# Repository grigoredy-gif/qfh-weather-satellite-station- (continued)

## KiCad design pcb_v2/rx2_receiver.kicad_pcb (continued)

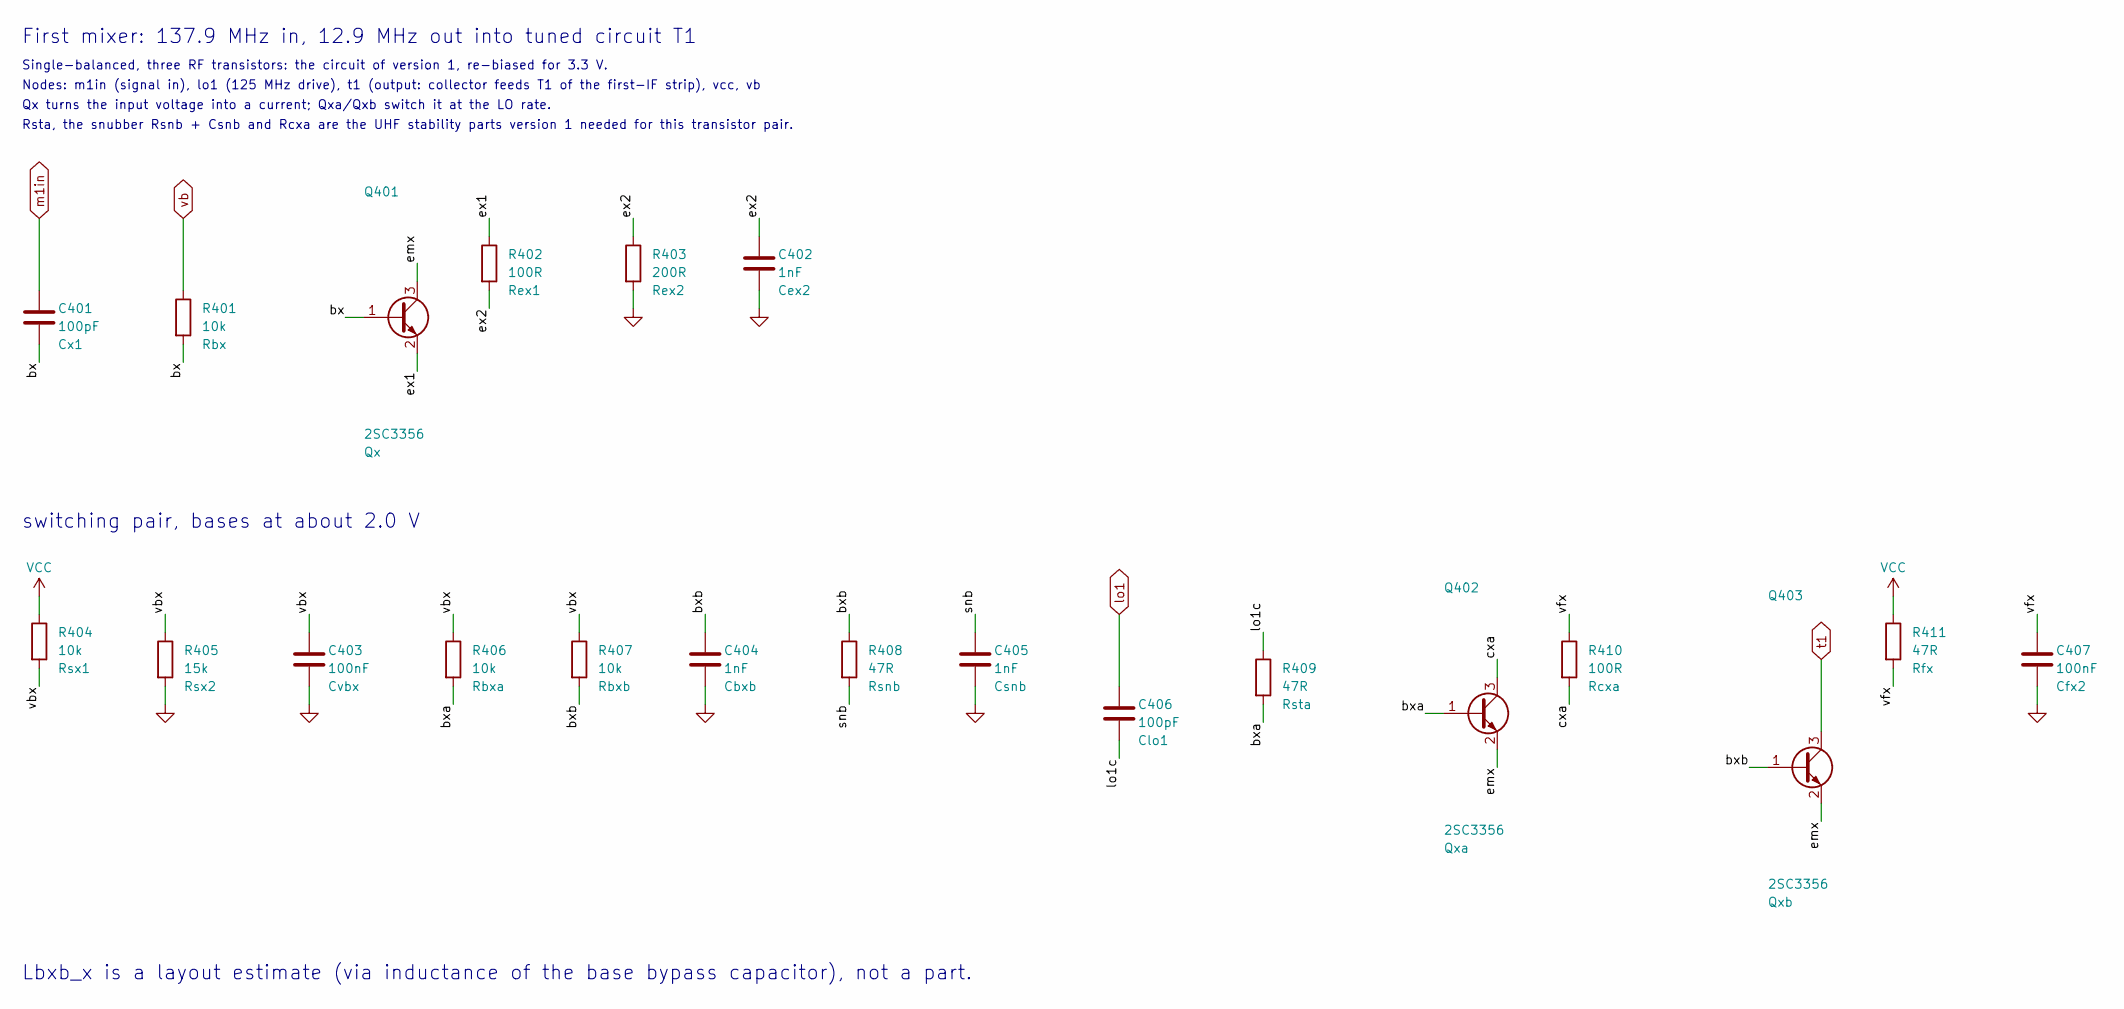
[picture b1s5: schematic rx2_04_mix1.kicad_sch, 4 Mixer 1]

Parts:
C401, C406: 100pF; C_0603_1608Metric; MPN CL10C101JB8NNNC; LCSC C14858
C402, C404, C405: 1nF; C_0603_1608Metric; MPN CL10B102KB8NNNC; LCSC C1588
C403, C407: 100nF; C_0603_1608Metric; MPN CC0603KRX7R9BB104; LCSC C14663
Q401, Q402, Q403: 2SC3356; SOT-23; MPN 2SC3356; LCSC C28646266
R401, R404, R406, R407: 10k; R_0603_1608Metric; MPN 0603WAF1002T5E; LCSC C25804
R402, R410: 100R; R_0603_1608Metric; MPN 0603WAF1000T5E; LCSC C22775
R403: 200R; R_0603_1608Metric; MPN 0603WAF2000T5E; LCSC C8218
R405: 15k; R_0603_1608Metric; MPN 0603WAF1502T5E; LCSC C22809
R408, R409, R411: 47R; R_0603_1608Metric; MPN 0603WAF470JT5E; LCSC C23182

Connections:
/4 Mixer 1/bx: C401.2, Q401.1 (B), R401.2
/4 Mixer 1/bxa: Q402.1 (B), R406.2, R409.2
/4 Mixer 1/bxb: C404.1, Q403.1 (B), R407.2, R408.1
/4 Mixer 1/cxa: Q402.3 (C), R410.2
/4 Mixer 1/emx: Q401.3 (C), Q402.2 (E), Q403.2 (E)
/4 Mixer 1/ex1: Q401.2 (E), R402.1
/4 Mixer 1/ex2: C402.1, R402.2, R403.1
/4 Mixer 1/lo1c: C406.2, R409.1
/4 Mixer 1/snb: C405.1, R408.2
/4 Mixer 1/vbx: C403.1, R404.2, R405.1, R406.1, R407.1
/4 Mixer 1/vfx: C407.1, R410.1, R411.2
GND: C402.2, C403.2, C404.2, C405.2, C407.2, R403.2, R405.2; also elsewhere on the board
VCC: R404.1, R411.1; also elsewhere on the board
lo1: C406.1; also elsewhere on the board
m1in: C401.1; also elsewhere on the board
t1: Q403.3 (C); also elsewhere on the board
vb: R401.1; also elsewhere on the board

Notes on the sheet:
First mixer: 137.9 MHz in, 12.9 MHz out into tuned circuit T1
Single-balanced, three RF transistors: the circuit of version 1, re-biased for 3.3 V.
Nodes: m1in (signal in), lo1 (125 MHz drive), t1 (output: collector feeds T1 of the first-IF strip), vcc, vb
Qx turns the input voltage into a current; Qxa/Qxb switch it at the LO rate.
Rsta, the snubber Rsnb + Csnb and Rcxa are the UHF stability parts version 1 needed for this transistor pair.
switching pair, bases at about 2.0 V
Lbxb_x is a layout estimate (via inductance of the base bypass capacitor), not a part.

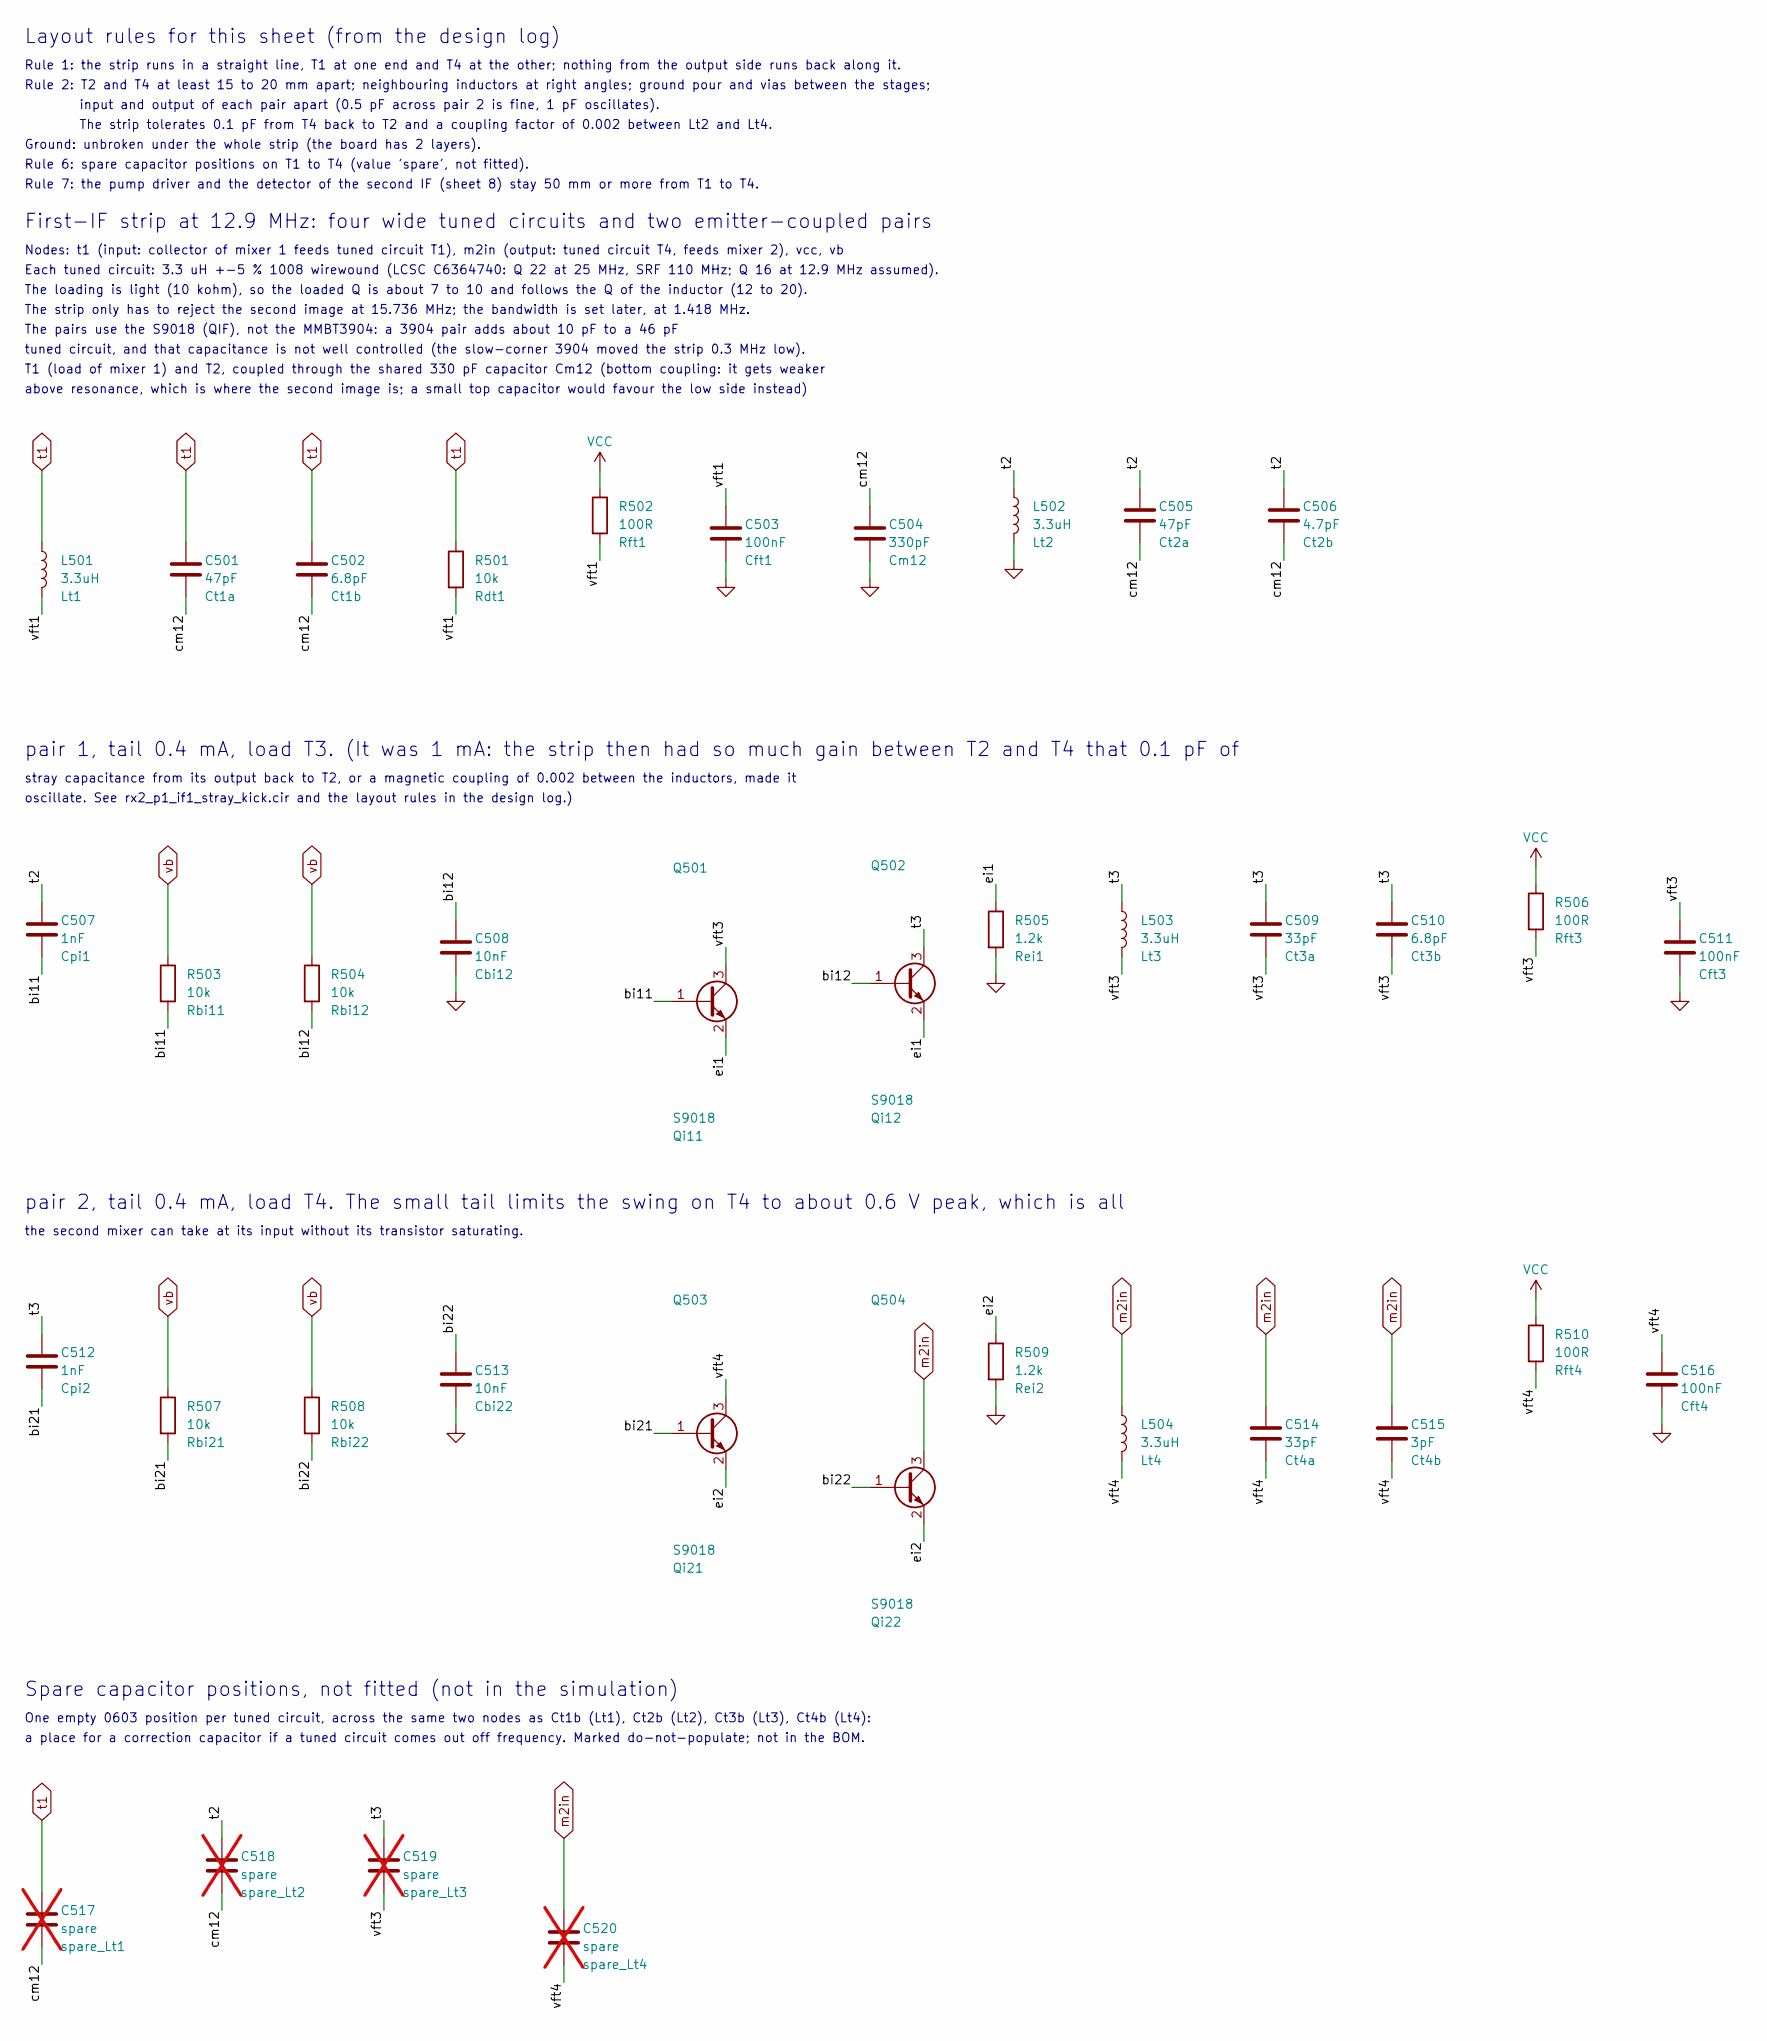
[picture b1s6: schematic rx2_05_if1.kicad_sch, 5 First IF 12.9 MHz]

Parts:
C501, C505: 47pF; C_0603_1608Metric; MPN CL10C470JB8NNNC; LCSC C1671
C502, C510: 6.8pF; C_0603_1608Metric; MPN 0603CG6R8C500NT; LCSC C1679
C503, C511, C516: 100nF; C_0603_1608Metric; MPN CC0603KRX7R9BB104; LCSC C14663
C504: 330pF; C_0603_1608Metric; MPN CL10C331JB8NNNC; LCSC C1664
C506: 4.7pF; C_0603_1608Metric; MPN 0603CG4R7C500NT; LCSC C1669
C507, C512: 1nF; C_0603_1608Metric; MPN CL10B102KB8NNNC; LCSC C1588
C508, C513: 10nF; C_0603_1608Metric; MPN 0603B103K500NT; LCSC C57112
C509, C514: 33pF; C_0603_1608Metric; MPN CL10C330JB8NNNC; LCSC C1663
C515: 3pF; C_0603_1608Metric; MPN 0603CG3R0C500NT; LCSC C46219
C517, C518, C519, C520: spare; C_0603_1608Metric; not fitted
L501, L502, L503, L504: 3.3uH; L_1008_AHW2520C; MPN AHW2520C-3R3JTF; LCSC C6364740
Q501, Q502, Q503, Q504: S9018; SOT-23; MPN S9018; LCSC C41375130
R501, R503, R504, R507, R508: 10k; R_0603_1608Metric; MPN 0603WAF1002T5E; LCSC C25804
R502, R506, R510: 100R; R_0603_1608Metric; MPN 0603WAF1000T5E; LCSC C22775
R505, R509: 1.2k; R_0603_1608Metric; MPN 0603WAF1201T5E; LCSC C22765

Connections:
/5 First IF 12.9 MHz/bi11: C507.2, Q501.1 (B), R503.2
/5 First IF 12.9 MHz/bi12: C508.1, Q502.1 (B), R504.2
/5 First IF 12.9 MHz/bi21: C512.2, Q503.1 (B), R507.2
/5 First IF 12.9 MHz/bi22: C513.1, Q504.1 (B), R508.2
/5 First IF 12.9 MHz/cm12: C501.2, C502.2, C504.1, C505.2, C506.2, C517.2, C518.2
/5 First IF 12.9 MHz/ei1: Q501.2 (E), Q502.2 (E), R505.1
/5 First IF 12.9 MHz/ei2: Q503.2 (E), Q504.2 (E), R509.1
/5 First IF 12.9 MHz/t2: C505.1, C506.1, C507.1, C518.1, L502.1
/5 First IF 12.9 MHz/t3: C509.1, C510.1, C512.1, C519.1, L503.1, Q502.3 (C)
/5 First IF 12.9 MHz/vft1: C503.1, L501.2, R501.2, R502.2
/5 First IF 12.9 MHz/vft3: C509.2, C510.2, C511.1, C519.2, L503.2, Q501.3 (C), R506.2
/5 First IF 12.9 MHz/vft4: C514.2, C515.2, C516.1, C520.2, L504.2, Q503.3 (C), R510.2
GND: C503.2, C504.2, C508.2, C511.2, C513.2, C516.2, L502.2, R505.2, R509.2; also elsewhere on the board
VCC: R502.1, R506.1, R510.1; also elsewhere on the board
m2in: C514.1, C515.1, C520.1, L504.1, Q504.3 (C); also elsewhere on the board
t1: C501.1, C502.1, C517.1, L501.1, R501.1; also elsewhere on the board
vb: R503.1, R504.1, R507.1, R508.1; also elsewhere on the board

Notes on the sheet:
Layout rules for this sheet (from the design log)
Rule 1: the strip runs in a straight line, T1 at one end and T4 at the other; nothing from the output side runs back along it.
Rule 2: T2 and T4 at least 15 to 20 mm apart; neighbouring inductors at right angles; ground pour and vias between the stages;
input and output of each pair apart (0.5 pF across pair 2 is fine, 1 pF oscillates).
The strip tolerates 0.1 pF from T4 back to T2 and a coupling factor of 0.002 between Lt2 and Lt4.
Ground: unbroken under the whole strip (the board has 2 layers).
Rule 6: spare capacitor positions on T1 to T4 (value 'spare', not fitted).
Rule 7: the pump driver and the detector of the second IF (sheet 8) stay 50 mm or more from T1 to T4.
First-IF strip at 12.9 MHz: four wide tuned circuits and two emitter-coupled pairs
Nodes: t1 (input: collector of mixer 1 feeds tuned circuit T1), m2in (output: tuned circuit T4, feeds mixer 2), vcc, vb
Each tuned circuit: 3.3 uH +-5 % 1008 wirewound (LCSC C6364740: Q 22 at 25 MHz, SRF 110 MHz; Q 16 at 12.9 MHz assumed).
The loading is light (10 kohm), so the loaded Q is about 7 to 10 and follows the Q of the inductor (12 to 20).
The strip only has to reject the second image at 15.736 MHz; the bandwidth is set later, at 1.418 MHz.
The pairs use the S9018 (QIF), not the MMBT3904: a 3904 pair adds about 10 pF to a 46 pF
tuned circuit, and that capacitance is not well controlled (the slow-corner 3904 moved the strip 0.3 MHz low).
T1 (load of mixer 1) and T2, coupled through the shared 330 pF capacitor Cm12 (bottom coupling: it gets weaker
above resonance, which is where the second image is; a small top capacitor would favour the low side instead)
pair 1, tail 0.4 mA, load T3. (It was 1 mA: the strip then had so much gain between T2 and T4 that 0.1 pF of
stray capacitance from its output back to T2, or a magnetic coupling of 0.002 between the inductors, made it
oscillate. See rx2_p1_if1_stray_kick.cir and the layout rules in the design log.)
pair 2, tail 0.4 mA, load T4. The small tail limits the swing on T4 to about 0.6 V peak, which is all
the second mixer can take at its input without its transistor saturating.
Spare capacitor positions, not fitted (not in the simulation)
One empty 0603 position per tuned circuit, across the same two nodes as Ct1b (Lt1), Ct2b (Lt2), Ct3b (Lt3), Ct4b (Lt4):
a place for a correction capacitor if a tuned circuit comes out off frequency. Marked do-not-populate; not in the BOM.

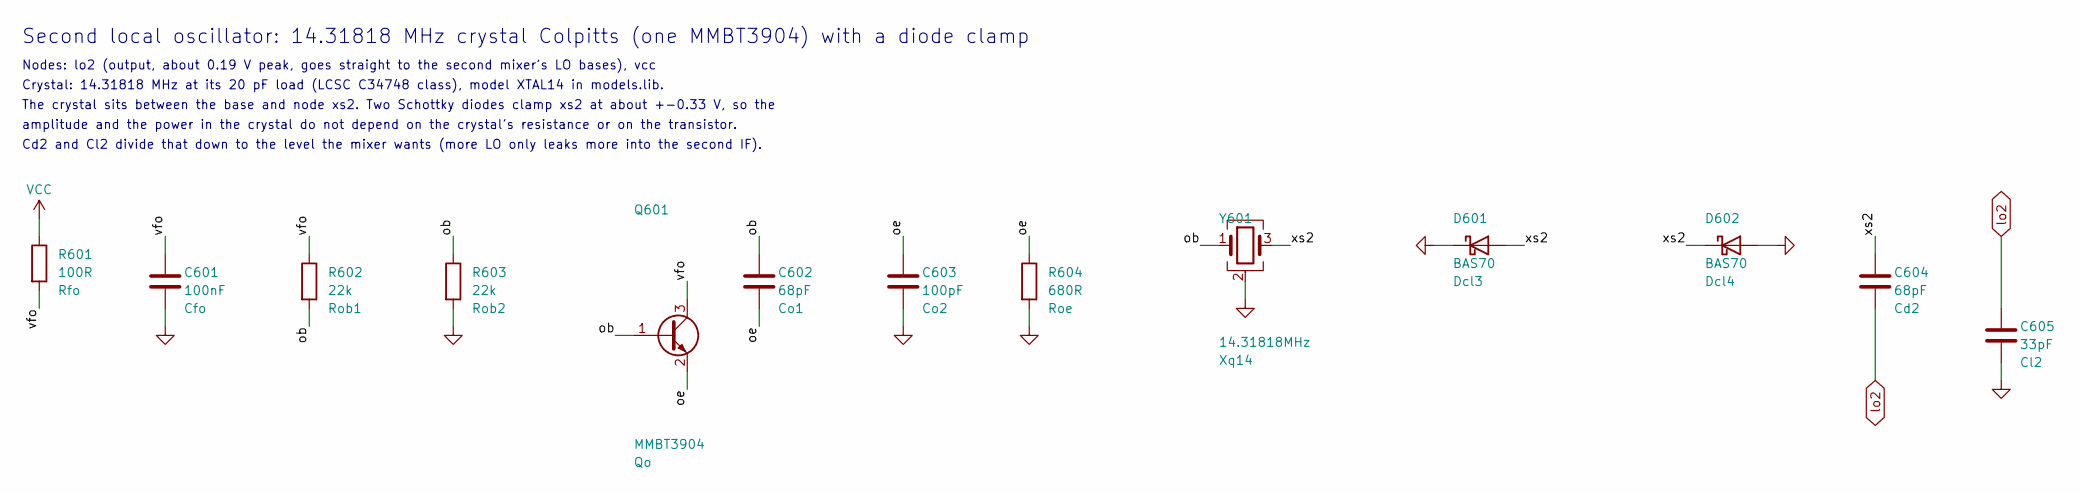
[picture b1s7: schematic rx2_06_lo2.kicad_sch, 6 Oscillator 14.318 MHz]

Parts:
C601: 100nF; C_0603_1608Metric; MPN CC0603KRX7R9BB104; LCSC C14663
C602, C604: 68pF; C_0603_1608Metric; MPN CL10C680JB8NNNC; LCSC C28262
C603: 100pF; C_0603_1608Metric; MPN CL10C101JB8NNNC; LCSC C14858
C605: 33pF; C_0603_1608Metric; MPN CL10C330JB8NNNC; LCSC C1663
D601, D602: BAS70; SOT-23; MPN BAS70; LCSC C7502686
Q601: MMBT3904; SOT-23; MPN MMBT3904(RANGE:100-300); LCSC C20526
R601: 100R; R_0603_1608Metric; MPN 0603WAF1000T5E; LCSC C22775
R602, R603: 22k; R_0603_1608Metric; MPN 0603WAF2202T5E; LCSC C31850
R604: 680R; R_0603_1608Metric; MPN 0603WAF6800T5E; LCSC C23228
Y601: 14.31818MHz; Crystal_SMD_3225-4Pin_3.2x2.5mm; MPN X32251431818MSB4SI; LCSC C34748

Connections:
/6 Oscillator 14.318 MHz/ob: C602.1, Q601.1 (B), R602.2, R603.1, Y601.1
/6 Oscillator 14.318 MHz/oe: C602.2, C603.1, Q601.2 (E), R604.1
/6 Oscillator 14.318 MHz/vfo: C601.1, Q601.3 (C), R601.2, R602.1
/6 Oscillator 14.318 MHz/xs2: C604.1, D601.1 (A), D602.3 (K), Y601.3
GND: C601.2, C603.2, C605.2, D601.3 (K), D602.1 (A), R603.2, R604.2, Y601.2 (G), Y601.4 (G); also elsewhere on the board
VCC: R601.1; also elsewhere on the board
lo2: C604.2, C605.1; also elsewhere on the board

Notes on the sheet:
Second local oscillator: 14.31818 MHz crystal Colpitts (one MMBT3904) with a diode clamp
Nodes: lo2 (output, about 0.19 V peak, goes straight to the second mixer's LO bases), vcc
Crystal: 14.31818 MHz at its 20 pF load (LCSC C34748 class), model XTAL14 in models.lib.
The crystal sits between the base and node xs2. Two Schottky diodes clamp xs2 at about +-0.33 V, so the
amplitude and the power in the crystal do not depend on the crystal's resistance or on the transistor.
Cd2 and Cl2 divide that down to the level the mixer wants (more LO only leaks more into the second IF).

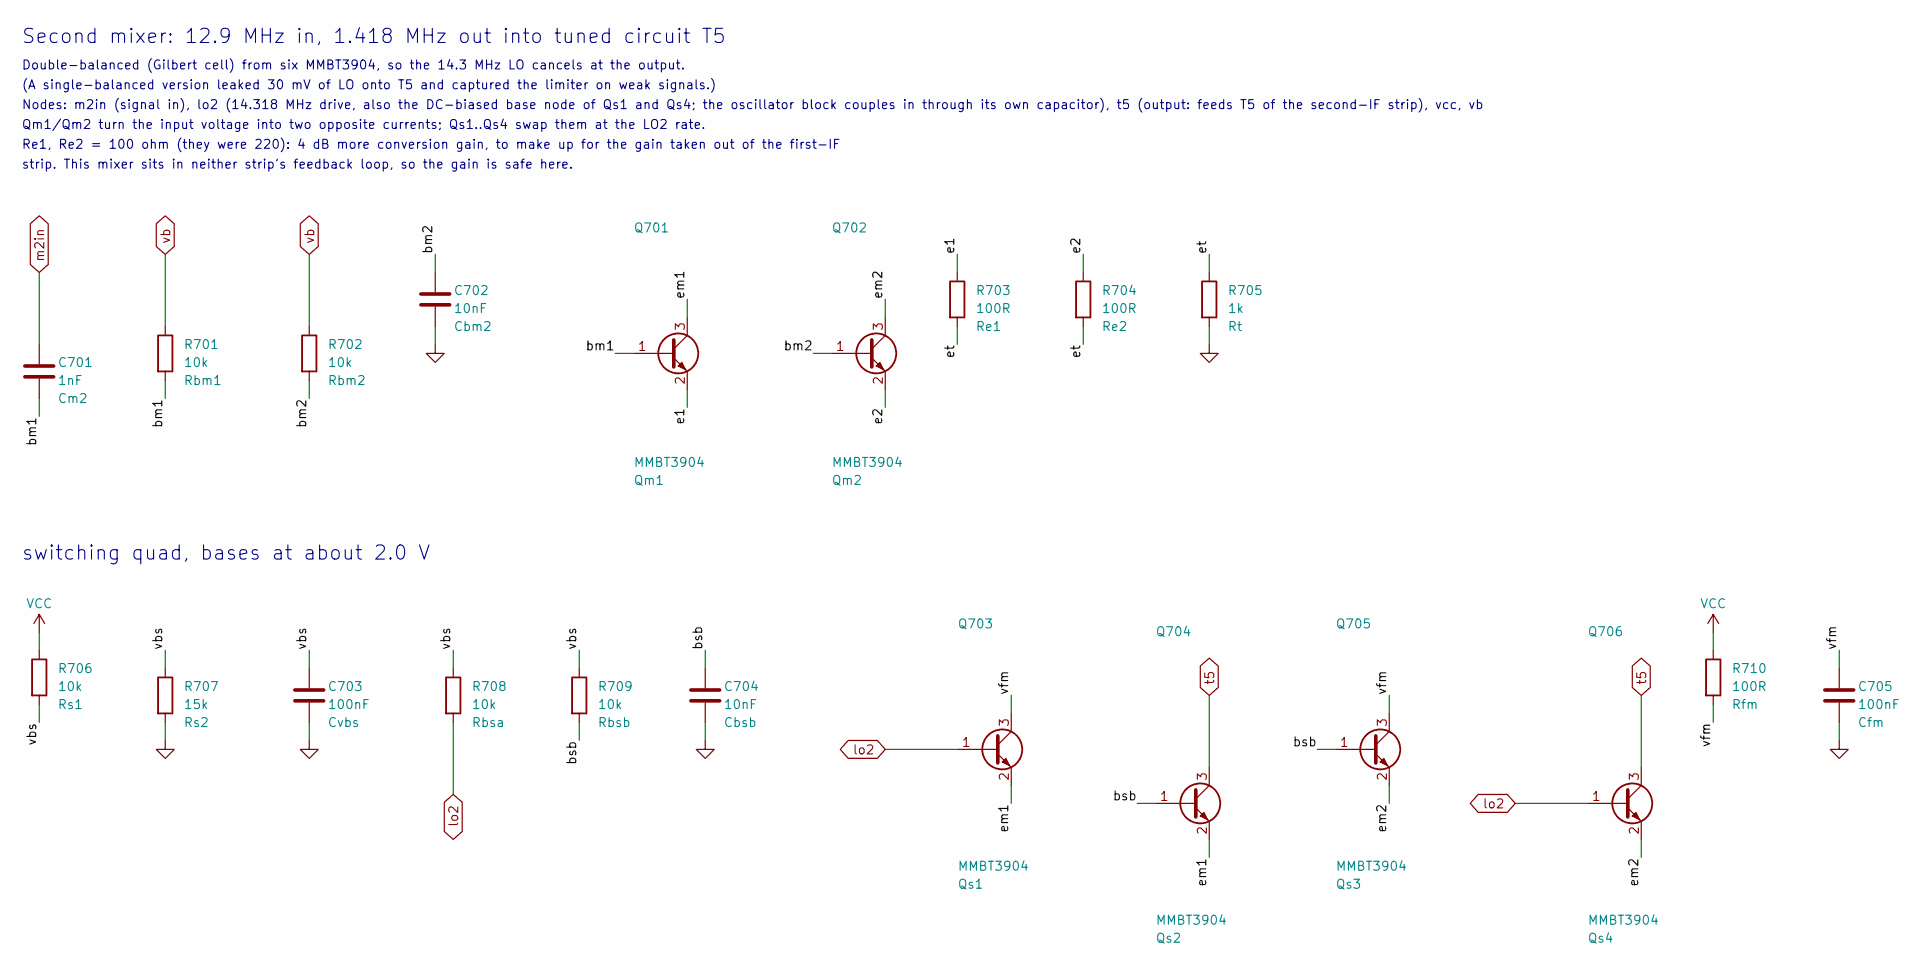
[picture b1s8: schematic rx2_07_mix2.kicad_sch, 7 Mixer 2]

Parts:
C701: 1nF; C_0603_1608Metric; MPN CL10B102KB8NNNC; LCSC C1588
C702, C704: 10nF; C_0603_1608Metric; MPN 0603B103K500NT; LCSC C57112
C703, C705: 100nF; C_0603_1608Metric; MPN CC0603KRX7R9BB104; LCSC C14663
Q701, Q702, Q703, Q704, Q705, Q706: MMBT3904; SOT-23; MPN MMBT3904(RANGE:100-300); LCSC C20526
R701, R702, R706, R708, R709: 10k; R_0603_1608Metric; MPN 0603WAF1002T5E; LCSC C25804
R703, R704, R710: 100R; R_0603_1608Metric; MPN 0603WAF1000T5E; LCSC C22775
R705: 1k; R_0603_1608Metric; MPN 0603WAF1001T5E; LCSC C21190
R707: 15k; R_0603_1608Metric; MPN 0603WAF1502T5E; LCSC C22809

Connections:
/7 Mixer 2/bm1: C701.2, Q701.1 (B), R701.2
/7 Mixer 2/bm2: C702.1, Q702.1 (B), R702.2
/7 Mixer 2/bsb: C704.1, Q704.1 (B), Q705.1 (B), R709.2
/7 Mixer 2/e1: Q701.2 (E), R703.1
/7 Mixer 2/e2: Q702.2 (E), R704.1
/7 Mixer 2/em1: Q701.3 (C), Q703.2 (E), Q704.2 (E)
/7 Mixer 2/em2: Q702.3 (C), Q705.2 (E), Q706.2 (E)
/7 Mixer 2/et: R703.2, R704.2, R705.1
/7 Mixer 2/vbs: C703.1, R706.2, R707.1, R708.1, R709.1
/7 Mixer 2/vfm: C705.1, Q703.3 (C), Q705.3 (C), R710.2
GND: C702.2, C703.2, C704.2, C705.2, R705.2, R707.2; also elsewhere on the board
VCC: R706.1, R710.1; also elsewhere on the board
lo2: Q703.1 (B), Q706.1 (B), R708.2; also elsewhere on the board
m2in: C701.1; also elsewhere on the board
t5: Q704.3 (C), Q706.3 (C); also elsewhere on the board
vb: R701.1, R702.1; also elsewhere on the board

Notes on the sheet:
Second mixer: 12.9 MHz in, 1.418 MHz out into tuned circuit T5
Double-balanced (Gilbert cell) from six MMBT3904, so the 14.3 MHz LO cancels at the output.
(A single-balanced version leaked 30 mV of LO onto T5 and captured the limiter on weak signals.)
Nodes: m2in (signal in), lo2 (14.318 MHz drive, also the DC-biased base node of Qs1 and Qs4; the oscillator block couples in through its own capacitor), t5 (output: feeds T5 of the second-IF strip), vcc, vb
Qm1/Qm2 turn the input voltage into two opposite currents; Qs1..Qs4 swap them at the LO2 rate.
Re1, Re2 = 100 ohm (they were 220): 4 dB more conversion gain, to make up for the gain taken out of the first-IF
strip. This mixer sits in neither strip's feedback loop, so the gain is safe here.
switching quad, bases at about 2.0 V

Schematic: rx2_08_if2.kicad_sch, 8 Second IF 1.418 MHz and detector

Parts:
C801, C806: 100pF; C_0603_1608Metric; MPN CL10C101JB8NNNC; LCSC C14858
C802: 4.7pF; C_0603_1608Metric; MPN 0603CG4R7C500NT; LCSC C1669
C803, C808, C811, C814: 100nF; C_0603_1608Metric; MPN CC0603KRX7R9BB104; LCSC C14663
C804, C809: 1nF; C_0603_1608Metric; MPN CL10B102KB8NNNC; LCSC C1588
C805, C810, C812, C813: 10nF; C_0603_1608Metric; MPN 0603B103K500NT; LCSC C57112
C807: 6.8pF; C_0603_1608Metric; MPN 0603CG6R8C500NT; LCSC C1679
C815: 1uF; C_0603_1608Metric; MPN CL10A105KB8NNNC; LCSC C15849
C816: 47pF; C_0603_1608Metric; MPN CL10C470JB8NNNC; LCSC C1671
C817: 470pF; C_0603_1608Metric; MPN 0603B471K500NT; LCSC C1620
C818, C819: spare; C_0603_1608Metric; not fitted
D801: BAS70; SOT-23; MPN BAS70; LCSC C7502686
L801, L802: 100uH; L_1210_NLV32; MPN NLV32T-101J-EF; LCSC C295124
Q801, Q802, Q803, Q804, Q805, Q806: MMBT3904; SOT-23; MPN MMBT3904(RANGE:100-300); LCSC C20526
Q807: MMBT3906; SOT-23; MPN MMBT3906; LCSC C7420354
R801, R805, R810: 100R; R_0603_1608Metric; MPN 0603WAF1000T5E; LCSC C22775
R802, R803, R806, R807, R811: 10k; R_0603_1608Metric; MPN 0603WAF1002T5E; LCSC C25804
R804, R814: 1.1k; R_0603_1608Metric; MPN 0603WAF1101T5E; LCSC C22764
R808: 560R; R_0603_1608Metric; MPN 0603WAF5600T5E; LCSC C23204
R809: 1.8k; R_0603_1608Metric; MPN 0603WAF1801T5E; LCSC C4177
R812: 470R; R_0603_1608Metric; MPN 0603WAF4700T5E; LCSC C23179
R813: 390R; R_0603_1608Metric; MPN 0603WAF3900T5E; LCSC C23151
R815: 47R; R_0603_1608Metric; MPN 0603WAF470JT5E; LCSC C23182
R816: 1.5k; R_0603_1608Metric; MPN 0603WAF1501T5E; LCSC C22843
R817: 3k; R_0603_1608Metric; MPN 0603WAF3001T5E; LCSC C4211
R818: 27k; R_0603_1608Metric; MPN 0603WAF2702T5E; LCSC C22967

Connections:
/8 Second IF 1.418 MHz and detector/ba1: C804.2, Q801.1 (B), R802.2
/8 Second IF 1.418 MHz and detector/ba2: C805.1, Q802.1 (B), R803.2
/8 Second IF 1.418 MHz and detector/bb1: C809.2, Q803.1 (B), R806.2
/8 Second IF 1.418 MHz and detector/bb2: C810.1, Q804.1 (B), R807.2
/8 Second IF 1.418 MHz and detector/bc1: C812.2, Q805.1 (B), R811.2
/8 Second IF 1.418 MHz and detector/bc2: C813.1, Q806.1 (B), R812.2
/8 Second IF 1.418 MHz and detector/c2: C816.1, Q806.3 (C), R814.2
/8 Second IF 1.418 MHz and detector/cb: C812.1, Q804.3 (C), R809.2
/8 Second IF 1.418 MHz and detector/ea: Q801.2 (E), Q802.2 (E), R804.1
/8 Second IF 1.418 MHz and detector/eb: Q803.2 (E), Q804.2 (E), R808.1
/8 Second IF 1.418 MHz and detector/ec: Q805.2 (E), Q806.2 (E), R813.1
/8 Second IF 1.418 MHz and detector/t6: C806.1, C807.1, C809.1, C819.1, L802.1, Q802.3 (C)
/8 Second IF 1.418 MHz and detector/vf5: C801.2, C802.2, C803.1, C818.2, L801.2, R801.2
/8 Second IF 1.418 MHz and detector/vfa: C806.2, C807.2, C808.1, C819.2, L802.2, Q801.3 (C), R805.2
/8 Second IF 1.418 MHz and detector/vfb: C811.1, Q803.3 (C), R809.1, R810.2
/8 Second IF 1.418 MHz and detector/vfc: C814.1, Q805.3 (C), R814.1, R815.2, R816.1
/8 Second IF 1.418 MHz and detector/vp: C815.1, D801.1 (A), Q807.1 (B), R816.2, R817.1
/8 Second IF 1.418 MHz and detector/x: C816.2, D801.3 (K), Q807.2 (E)
GND: C803.2, C805.2, C808.2, C810.2, C811.2, C813.2, C814.2, C815.2, C817.2, R804.2, R808.2, R813.2, R817.2, R818.2; also elsewhere on the board
VCC: R801.1, R805.1, R810.1, R815.1; also elsewhere on the board
det: C817.1, Q807.3 (C), R818.1; also elsewhere on the board
t5: C801.1, C802.1, C804.1, C818.1, L801.1; also elsewhere on the board
vb: R802.1, R803.1, R806.1, R807.1; also elsewhere on the board
vbd: R811.1, R812.1; also elsewhere on the board

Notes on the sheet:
Layout rules for this sheet (from the design log)
Rule 1: the strip runs in a straight line, T5 / L5 at one end, the pump driver (pair C) and the detector at the other.
Rule 3: node 'c2' carries a 1.65 V square wave and 0.005 pF from 'c2' to T5 closes the loop: keep pair C and the detector
25 mm or more from T5 / L5, solid ground under and between, 'c2' and 'x' as short as possible,
L5 and L6 apart and at right angles (coupling factor under 0.007), T6 to T5 under 1 pF.
Ground: unbroken under the whole strip (the board has 2 layers).
Rule 6: spare capacitor positions on T5 and T6 (value 'spare', not fitted).
Rule 7: pair C and the detector 50 mm or more from the first-IF tuned circuits (sheet 5), unbroken ground between:
the 9th harmonic of c2 lies in the first IF, and the second IF can lock itself at LO2 / 10 = 1.4318 MHz.
Second-IF strip at 1.418 MHz: tuned circuit T5, pair A + tuned circuit T6, limiter pair B,
pump-driver pair C, charge-pump detector.
Nodes: vcc (3.3 V rail), t5 (input: collector of mixer 2 feeds this tuned circuit), det (detector output),
vb and vbd (the two references from rx2_blk_bias.inc)
T5: 100 uH (Q 30 at 1.4 MHz, 4 pF self-capacitance) with 100 pF + 4.7 pF; T6 the same with 100 pF + 6.8 pF.
The small capacitors centre the pair on 1.418 MHz with the second mixer connected and 1 pF of board stray
on each tuned circuit (Ct5_x, Ct6_x: layout estimates, not parts).
pair A, tail 0.5 mA, load T6
pair B, limiter, tail 1 mA, resistive load
pair C, pump driver, tail 1.6 mA: square wave of about 1.65 V at c2. Its bases hang on vbd, not on vb:
vbd follows the two junction drops the charge pump loses, so the detector output does not drift with temperature.
Its reference base goes to vbd through only 470 ohm, so the square-wave height does not depend on transistor gain.
charge pump: one packet of charge per cycle through Q3 into RL
Spare capacitor positions, not fitted (not in the simulation)
One empty 0603 position per tuned circuit, across the same two nodes as C5b (L5), C6b (L6):
a place for a correction capacitor if a tuned circuit comes out off frequency. Marked do-not-populate; not in the BOM.

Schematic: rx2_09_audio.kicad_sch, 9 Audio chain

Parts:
C901, C907: 100uF; C_1206_3216Metric; MPN CL31A107MQHNNNE; LCSC C15008
C902, C904: 4.7nF; C_0603_1608Metric; MPN 0603B472K500NT; LCSC C53987
C903, C905, C909: 1nF; C_0603_1608Metric; MPN CL10B102KB8NNNC; LCSC C1588
C906, C908: 1uF; C_0603_1608Metric; MPN CL10A105KB8NNNC; LCSC C15849
Q901, Q903: MMBT3906; SOT-23; MPN MMBT3906; LCSC C7420354
Q902, Q904: MMBT3904; SOT-23; MPN MMBT3904(RANGE:100-300); LCSC C20526
R901: 100R; R_0603_1608Metric; MPN 0603WAF1000T5E; LCSC C22775
R902: 10k; R_0603_1608Metric; MPN 0603WAF1002T5E; LCSC C25804
R903, R906: 15k; R_0603_1608Metric; MPN 0603WAF1502T5E; LCSC C22809
R904, R907: 5.6k; R_0603_1608Metric; MPN 0603WAF5601T5E; LCSC C23189
R905: 2.7k; R_0603_1608Metric; MPN 0603WAF2701T5E; LCSC C13167
R908: 2.2k; R_0603_1608Metric; MPN 0603WAF2201T5E; LCSC C4190
R909: 27k; R_0603_1608Metric; MPN 0603WAF2702T5E; LCSC C22967
R910: 22k; R_0603_1608Metric; MPN 0603WAF2202T5E; LCSC C31850
R911: 3k; R_0603_1608Metric; MPN 0603WAF3001T5E; LCSC C4211
R912: 47R; R_0603_1608Metric; MPN 0603WAF470JT5E; LCSC C23182
R913: 1.5k; R_0603_1608Metric; MPN 0603WAF1501T5E; LCSC C22843
R914: 82k; R_0603_1608Metric; MPN 0603WAF8202T5E; LCSC C23254
R915: 51k; R_0603_1608Metric; MPN 0603WAF5102T5E; LCSC C23196

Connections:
/9 Audio chain/bg: C906.2, Q904.1 (B), R909.2, R910.1
/9 Audio chain/cg: C908.1, Q904.3 (C), R911.2
/9 Audio chain/ea1: Q901.2 (E), R902.2, R903.1
/9 Audio chain/ea2: C902.2, Q902.2 (E), R905.1, R906.1
/9 Audio chain/ea3: C904.2, C906.1, Q903.2 (E), R908.2
/9 Audio chain/eg: Q904.2 (E), R912.1
/9 Audio chain/eg2: C907.1, R912.2, R913.1
/9 Audio chain/n11: C902.1, R903.2, R904.1
/9 Audio chain/n21: C904.1, R906.2, R907.1
/9 Audio chain/ub2: C903.1, Q902.1 (B), R904.2
/9 Audio chain/ub3: C905.1, Q903.1 (B), R907.2
/9 Audio chain/va: C901.1, Q902.3 (C), R901.2, R902.1, R908.1, R909.1, R911.1, R914.1
GND: C901.2, C903.2, C905.2, C907.2, C909.2, Q901.3 (C), Q903.3 (C), R905.2, R910.2, R913.2, R915.2; also elsewhere on the board
VCC: R901.1; also elsewhere on the board
adc: C908.2, C909.1, R914.2, R915.1; also elsewhere on the board
det: Q901.1 (B); also elsewhere on the board

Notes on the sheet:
Layout rules for this sheet (from the design log)
Rule 5: Cadc sits at the DevKitC pin (GPIO36 = pin 3 of the left socket, sheet 10), away from T6 and node 'c2'.
Audio chain: buffer, 4th-order low-pass (two Sallen-Key sections), gain stage, ADC interface
Nodes: det (detector output: 1.27 V DC, 27 kohm source, about 10 mV peak of audio), adc (to ESP32 GPIO36), vcc
Followers alternate PNP / NPN / PNP so the DC level steps up, down, up and nothing needs a coupling capacitor
until the gain stage. The gain stage is AC-coupled on both sides, so its own DC drift does not reach the ADC.
Gain stage: base at 1.45 V, emitter at 0.8 V, collector at about 1.7 V, so it has room to swing both ways at
every corner. The rest level at the ADC pin (1.25 V) comes from the filtered audio supply va, not from the
3V3 pin: ripple on that pin would otherwise reach the ADC only 26 dB down.

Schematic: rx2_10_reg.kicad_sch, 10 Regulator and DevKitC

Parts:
C1001, C1002: 10uF; C_0603_1608Metric; MPN CL10A106KP8NNNC; LCSC C19702
C1003: 100uF; C_1206_3216Metric; MPN CL31A107MQHNNNE; LCSC C15008
J1001: DevKitC_left; PinSocket_1x19_P2.54mm_Vertical; MPN KH-2.54FH-1X19P-H8.5; LCSC C2932678
J1002: DevKitC_right; PinSocket_1x19_P2.54mm_Vertical; MPN KH-2.54FH-1X19P-H8.5; LCSC C2932678
Q1001, Q1002: MMBT3906; SOT-23; MPN MMBT3906; LCSC C7420354
Q1003, Q1004: MMBT3904; SOT-23; MPN MMBT3904(RANGE:100-300); LCSC C20526
R1001: 10R; R_0603_1608Metric; MPN 0603WAF100JT5E; LCSC C22859
R1002: 1.5k; R_0603_1608Metric; MPN 0603WAF1501T5E; LCSC C22843
R1003: 1.2k; R_0603_1608Metric; MPN 0603WAF1201T5E; LCSC C22765
R1004: 2.2k; R_0603_1608Metric; MPN 0603WAF2201T5E; LCSC C4190

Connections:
/10 Regulator and DevKitC/pb: Q1001.3 (C), Q1002.1 (B), Q1003.3 (C), R1002.2
/10 Regulator and DevKitC/pe: Q1001.1 (B), Q1002.2 (E), Q1004.3 (C), R1001.2, R1002.1
/10 Regulator and DevKitC/ret: Q1003.2 (E), Q1004.2 (E), R1003.1
/10 Regulator and DevKitC/v3ref: J1001.1, R1004.1
/10 Regulator and DevKitC/v5: C1002.1, J1001.19, Q1001.2 (E), R1001.1
/10 Regulator and DevKitC/vref: C1001.1, Q1003.1 (B), R1004.2
GND: C1001.2, C1002.2, C1003.2, J1001.14, J1002.1, J1002.7, R1003.2; also elsewhere on the board
VCC: C1003.1, Q1002.3 (C), Q1004.1 (B); also elsewhere on the board
adc: J1001.3; also elsewhere on the board

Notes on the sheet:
Layout rules for this sheet (from the design log)
Rule 5: Cadc (sheet 9) sits at pin 3 of the left DevKitC socket.
3.3 V rail: discrete regulator that copies the DevKitC's 3V3 pin
Nodes: v5 (DevKitC 5V pin, 4.2 to 5 V), v3ref (DevKitC 3V3 pin), vcc (receiver rail, about 3.28 V)
The power comes from the 5V pin through the PNP pass transistor Qrp. The voltage is set by the 3V3 pin,
filtered by Rr1 and Cr (7 Hz), so the ESP32's own supply noise does not reach the receiver.
Qre1 and Qre2 compare the rail with that reference and drive Qrp. Rrs and Qrl limit the current to about 65 mA.
ESP32 DevKitC, 38 pins (not in the simulation)
Two 1x19 sockets, 2.54 mm, soldered by hand (LCSC C2932678); the DevKitC plugs in. Rows 25.4 mm apart, as on version 1.
Pins used (Espressif's pin table of the DevKitC V4): left row J2 pin 1 = 3V3 (v3ref), pin 3 = GPIO36 / VP (adc), pin 14 = GND,
pin 19 = 5V (v5); right row J3 pins 1 and 7 = GND. Pin 1 is at the antenna end of the module. All other pins stay free.
Power flags (they only tell the electrical rules check that GND and VCC are driven)

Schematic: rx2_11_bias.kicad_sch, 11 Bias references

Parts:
C1101, C1102: 10uF; C_0603_1608Metric; MPN CL10A106KP8NNNC; LCSC C19702
Q1101, Q1102: MMBT3904; SOT-23; MPN MMBT3904(RANGE:100-300); LCSC C20526
Q1103: MMBT3906; SOT-23; MPN MMBT3906; LCSC C7420354
R1101: 1.1k; R_0603_1608Metric; MPN 0603WAF1101T5E; LCSC C22764
R1102: 270R; R_0603_1608Metric; MPN 0603WAF2700T5E; LCSC C22966
R1103: 4.7k; R_0603_1608Metric; MPN 0603WAF4701T5E; LCSC C23162

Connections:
/11 Bias references/vbdm: Q1102.2 (E), Q1103.2 (E)
/11 Bias references/vbr: Q1101.2 (E), R1102.1
GND: C1101.2, C1102.2, Q1103.1 (B), Q1103.3 (C), R1102.2; also elsewhere on the board
VCC: R1101.1, R1103.1; also elsewhere on the board
vb: C1101.1, Q1101.1 (B), Q1101.3 (C), R1101.2; also elsewhere on the board
vbd: C1102.1, Q1102.1 (B), Q1102.3 (C), R1103.2; also elsewhere on the board

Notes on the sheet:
The two bias references
Nodes: vcc, vb, vbd
vb (about 1.17 V): shared by every emitter-coupled pair, both mixers and the squarer's current source.
One MMBT3904 connected as a diode on top of a 270 ohm resistor. The voltage across a stage's tail resistor is
vb minus one base-emitter drop, so the two junction drops cancel and what is left is the resistor drop
(about 0.5 V, a fixed fraction of the rail). Stage currents hold within a few percent over temperature.
vbd (about 1.27 V): for the pump driver (pair C in rx2_blk_if2.inc) only. An MMBT3904 and an MMBT3906 as diodes
in series. The charge pump loses two junction drops per cycle (its Schottky diode and its PNP), and those
drops fall as the board warms up. vbd falls with them, so the square wave shrinks by the same amount and
the detector output stays where it is.
